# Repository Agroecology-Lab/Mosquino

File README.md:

# Mosquino - UNTESTED
Smol BLDC driver 2.5A peak

The Mosquino is a fully self-contained, miniature 2.5-A, 8V-24V DC Triple 1/2-H Bridge Driver integrated on a board with an STM32G071 microcontroller. The board
provides three individually controllable half-H-bridge drivers. The Mosquino device is intended to drive a three-phase brushless-DC motor,

Originally in EasyEDA [Schematic](https://easyeda.com/editor#id=8d445a35637942748ff2db03f9d90374) [PCB](https://easyeda.com/editor#id=cbecfc11252747c5817d41da00d140a0)

Converted to Kicad and uploaded here. Designed for [SimpleFOC](https://community.simplefoc.com/search?q=mosquino) and [Yukon carrier](https://shop.pimoroni.com/products/yukon?variant=41185258111059) by Pimoroni

As it is a derviative of the [Mosquito](https://community.simplefoc.com/t/mosquito-board-new-design/1621/22?u=sam) board the [Mosquito manual](https://drive.google.com/file/u/1/d/1Ev1wcCPXnmiUsTl4JunoNijvsclqJlB7/view) should largely apply

Suitable motors might include [GB2208 from T-motor](https://s.click.aliexpress.com/e/_c35e97nl) It is designed to be plug and play with encoders from [Small robots on Tindie](https://www.tindie.com/stores/smallrobots/)

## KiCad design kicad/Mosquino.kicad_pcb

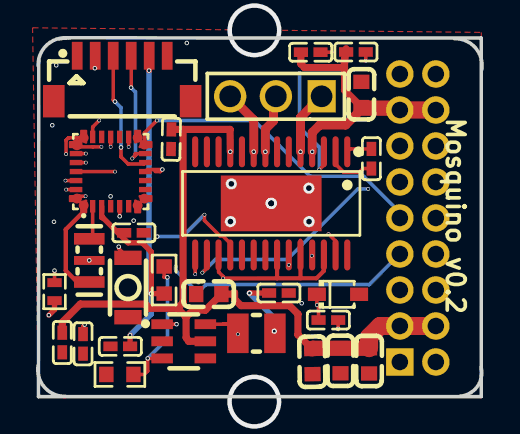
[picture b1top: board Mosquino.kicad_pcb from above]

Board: 4 copper layers, 24.7 x 19.9 mm, 29 parts (0 on the bottom side), 31 nets.

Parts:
C1, C2, C3, C11, C14, C15: 100nF; C0402
C4: 470nF; C0402
C5, C8, C9, C10, C12: 10uF; C0603
C6: 10uF; C0402
C7: 10nF; C0402
C13: 100nF; C0402_NEW
D1: 1N5819WS; SOD-323_L1.8-W1.3-LS2.5-RD
H1: HDR-TH_3P-P2.54-V-M-1
L5: 3.3uH; IND-SMD_L2.5-W2.0
OSHW_OSHW_6X100_NOTEXT3: OSHW_OSHW_6X100_NOTEXT
R4: 10kΩ; R0603
R6: 33kΩ; R0603
R12: 10K; R0402
RST1: TS-1049A-B2D4; SW-SMD_L3.0-W2.0-LS3.5
U1: MS8313; HTSSOP-28_L9.7-W4.4-P0.65-LS6.4-BL-EP
U2: C432211; UFQFPN-28_L4.0-W4.0-P0.50-BL
U5: LMR14006YDDCR; TSOT-23-6_L2.9-W1.6-P0.95-LS2.8-BL
U7: HDR-TH_18P-P2.00-V-M-R2-C9-S2.00
U8: CONN-SMD-6P-P1.00_BM06B-SRSS-TB-LF-SN
X1: 8MHz; OSC-SMD_3P-L3.2-W1.3-P1.2-L

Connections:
3V_VCC: C3.2, C6.2, C13.1, L5.2, R6.2, R12.2, U2.3, U7.10, U8.5
D1_1: C14.1, D1.1, L5.1, U5.6
DRESET: U1.16, U2.25
EN1: U1.17, U1.22, U1.24, U1.26, U2.22
FAULT: U1.18, U2.24
OSC_IN: U2.1, X1.3
OSC_OUT: U2.2, X1.1
PGND: C2.1, C3.1, C4.2, C5.1, C6.1, C8.1, C9.1, C10.1, C11.1, C12.1, C13.2, D1.2, R4.2, RST1.1, U1.6, U1.7, U1.10, U1.12, U1.13, U1.14, U1.19, U1.20, U1.21, U1.28, U1.29, U2.4, U5.2, U7.1, U7.2, U7.17, U7.18, U8.6, X1.2
PWM11: U1.27, U2.16
PWM12: U1.25, U2.18
PWM13: U1.23, U2.23
R6_1: R4.1, R6.1, U5.3
R12_1: R12.1, RST1.2, U2.5
SPI1_MISO: U2.12, U8.3
SPI1_MOSI: U2.13, U8.4
SPI1_SCK: U2.11, U8.2
SPI2_CSS: U2.14, U7.9
SPI2_MISO: U2.26, U7.11
SPI2_MOSI: U2.27, U7.5
SPI2_SCK: U2.28, U7.7
SWCLK: U2.21, U7.8
SWDIO: U2.20, U7.12
U1_1: C7.2, U1.1
U1_2: C7.1, U1.2
U1_3: C1.2, C15.2, U1.3
U1_5: H1.1, U1.5
U1_8: H1.2, U1.8
U1_9: H1.3, U1.9
U1_15: C4.1, U1.15
U5_1: C14.2, U5.1
VSUPP: C1.1, C2.2, C5.2, C8.2, C9.2, C10.2, C11.2, C12.2, C15.1, U1.4, U1.11, U5.5, U7.3, U7.4, U7.15, U7.16

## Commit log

2026-01-03 Update README with EasyEDA links
    Added links to original EasyEDA schematic and PCB.
2026-01-03 Create images
2026-01-03 Add PCB images to README
    Added images of the PCB to the README.
2026-01-03 Change license from MIT to CERN OHL v2
    Replaced MIT License with CERN Open Hardware Licence Version 2 - Strongly Reciprocal, including detailed terms and conditions.
2026-01-03 Update README with project status and carrier info
    Added 'UNTTESTED' to the project title and included a reference to the Yukon carrier by Pimoroni.
2026-01-03 Update README with new design references
2026-01-03 Update README with specifications and links
    Expanded the README to include detailed specifications and links.
2026-01-03 Update README with motor and encoder details
    Added information about suitable motors and plug-and-play encoders.

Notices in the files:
kicad/Mosquino.kicad_pcb:
CERN-OHL-S
